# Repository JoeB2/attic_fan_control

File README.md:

# attic_fan_control
Abstract:
  In the summer, Seattle Area, it can get hot.  Last summer, 2021 we saw several days well over 100f.
  Most homes in the Seattle area are not equiped with AC.  Attic space in my home can reach 130f degrees.
  If I could programatically manage an attic fan to turn on/off depending on Attic Temps & outside temps & inside house temps 
  it may reduce inside house temps.  (TBD)
  
  Using two ESP8266 -  ESP01:
  Control a solid state "relay" SSR-25 DA to turn on/off a box fan that covers an attic access in the ceiling.
  Using two Dallas DS18B20 temp sensors, one in the Attic and one in the hallway AND a remote esp01 sensor with a DS18B20
  the Attic esp01's C++ will determine whether to turn on the solid state module for the fan. 
  
Implementation:
  The Remote esp01 will be located in the shade outside in the back yard.  Its purpose will be to send outside
  temperatures to the Attic situated esp01, providing the c++ an opportunity to "imagine what's possible."
  The remote esp01 will have a single DS18B20 and a DS3231.
  
  Attic: esp01 handles 2x DS18B20 and a 2n2222 which excites a SSR-25 DA solid state relay.
    An NTP pool is contacted once every hour to get a current time value.
    Temperatures are checked and delta and threshold values are computed periodically based on a user provided value.
    A status web page is hosted which shows the various temperature values and the Fan On/Off status
    A setting page is hosted where a user can input threshold values for managing when the Fan is On/Off.
    Attic Master uses: WiFi STA mode, ESPNOW, WebSock, Relay, 2x DS18B20, WiFi AP_Mode when unable to connect to the SPIFFS stored SSID
    
    Fan on/Off Logic:
      1) Attic sensor: Threshold to force Fan on or off
      2) Attic sensor: compare self to inside to turn on/off fan
      3) Attic sensor: compare self to remote sensor to turn on/off fan
      4) Inside sensor: compare self to remote sensor to turn on/off fan
      Order of precidence: 1, 3, 4, 2.
      Setting any threshold value to zero dissables that check.
      
      NOTE:
        WiFi connectivity: The attic esp01 uses a JSON string stored in its SPIFFS {SSID, PWD, IP, GW, Mask, isDHCP}.
        If the esp01 failes to connect or if the SPIFFS JSON credential string fails the Attic esp01 goes into "AP_MODE"
        whereby a software AP SSID: "Attic Fan WiFi Setup: 10.0.1.23" is hosted.  Pointing a browser to the AP's IP will provide a page
        where an SSID, PWD, and preferred IP:GW:Mask can be entered.  If use DHCP is checked IP,GW, Mask are not used.

    Remote: esp01 handles a single DS18B20 temp sensor and a DS3231 clock.
      The temperature reading is entered into a struct along with the current time and the struct's binary bits are broadcast using ESPNOW.
      Upon reciving the remote's espnow broadcast the Attic esp01 will broadcast, using espnow, the same struct's bit with an updated ack bit and an updated time vale.

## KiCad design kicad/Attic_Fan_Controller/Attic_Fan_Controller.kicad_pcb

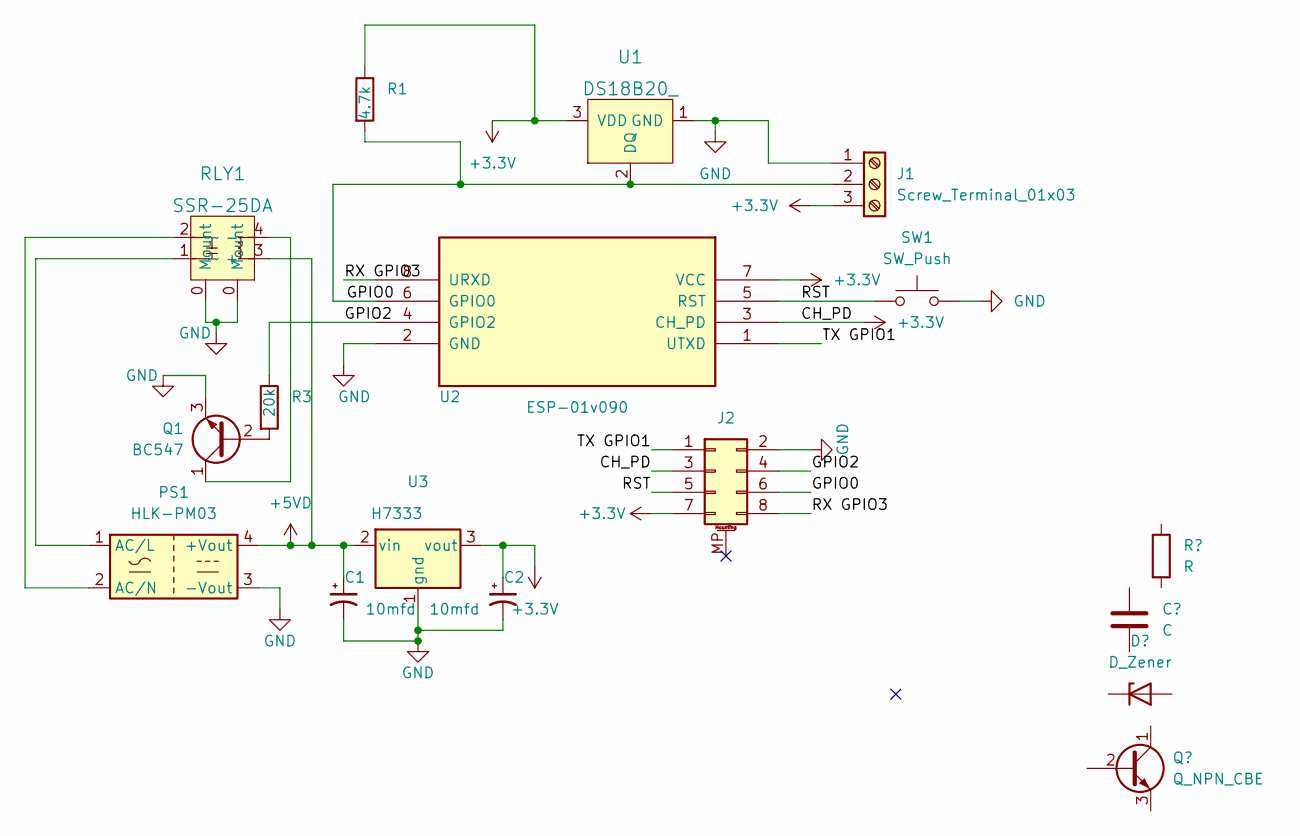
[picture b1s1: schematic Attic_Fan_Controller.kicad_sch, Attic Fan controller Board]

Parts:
C1, C2: 10mfd; CP_Radial_D4.0mm_P1.50mm
J1: Screw_Terminal_01x03; TerminalBlock_Phoenix_PT-1,5-3-5.0-H_1x03_P5.00mm_Horizontal
J2: Conn_02x04_Odd_Even_MountingPin; PinSocket_2x04_P2.54mm_Vertical
PS1: HLK-PM03; Converter_ACDC_HiLink_HLK-PMxx
Q1: BC547; TO-92_Inline
R1: 4.7k; R_Axial_DIN0207_L6.3mm_D2.5mm_P10.16mm_Horizontal
R3: 20k; R_Axial_DIN0207_L6.3mm_D2.5mm_P10.16mm_Horizontal
RLY1: SSR-25DA; SSR-25 DA; MPN 9007-05-00; Digi-Key_PN 306-1062-ND
SW1: SW_Push; SW_PUSH_6mm_H5mm
U1: DS18B20_; TO-92-3; MPN DS18B20+; Digi-Key_PN DS18B20+-ND
U2: ESP-01v090; ESP-01
U3: H7333; SOT-89-3

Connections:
+3V3: C2.1, J1.3, J2.3, J2.7, R1.1, U1.3 (VDD), U2.3 (CH_PD), U2.7 (VCC), U3.3 (vout); also elsewhere on the board
+5VD: C1.1, PS1.4 (+Vout), RLY1.3 (+), U3.2 (vin)
/GPIO0: J1.2, J2.6, R1.2, U1.2 (DQ), U2.6 (GPIO0)
/GPIO2: J2.4, R3.1, U2.4 (GPIO2); also elsewhere on the board
/RST: J2.5, SW1.1, U2.5 (RST)
/RX GPIO3: J2.8, U2.8 (URXD)
/TX GPIO1: J2.1, U2.1 (UTXD)
GND: C1.2, C2.2, J1.1, J2.2, PS1.3 (-Vout), Q1.3 (E), RLY1.0 (Mount), SW1.2, U1.1 (GND), U2.2 (GND), U3.1 (gnd)
unnamed: PS1.1 (AC/L), RLY1.1 (~~)
unnamed: PS1.2 (AC/N), RLY1.2 (~~)
unnamed: Q1.1 (C), RLY1.4 (-)
unnamed: Q1.2 (B), R3.2

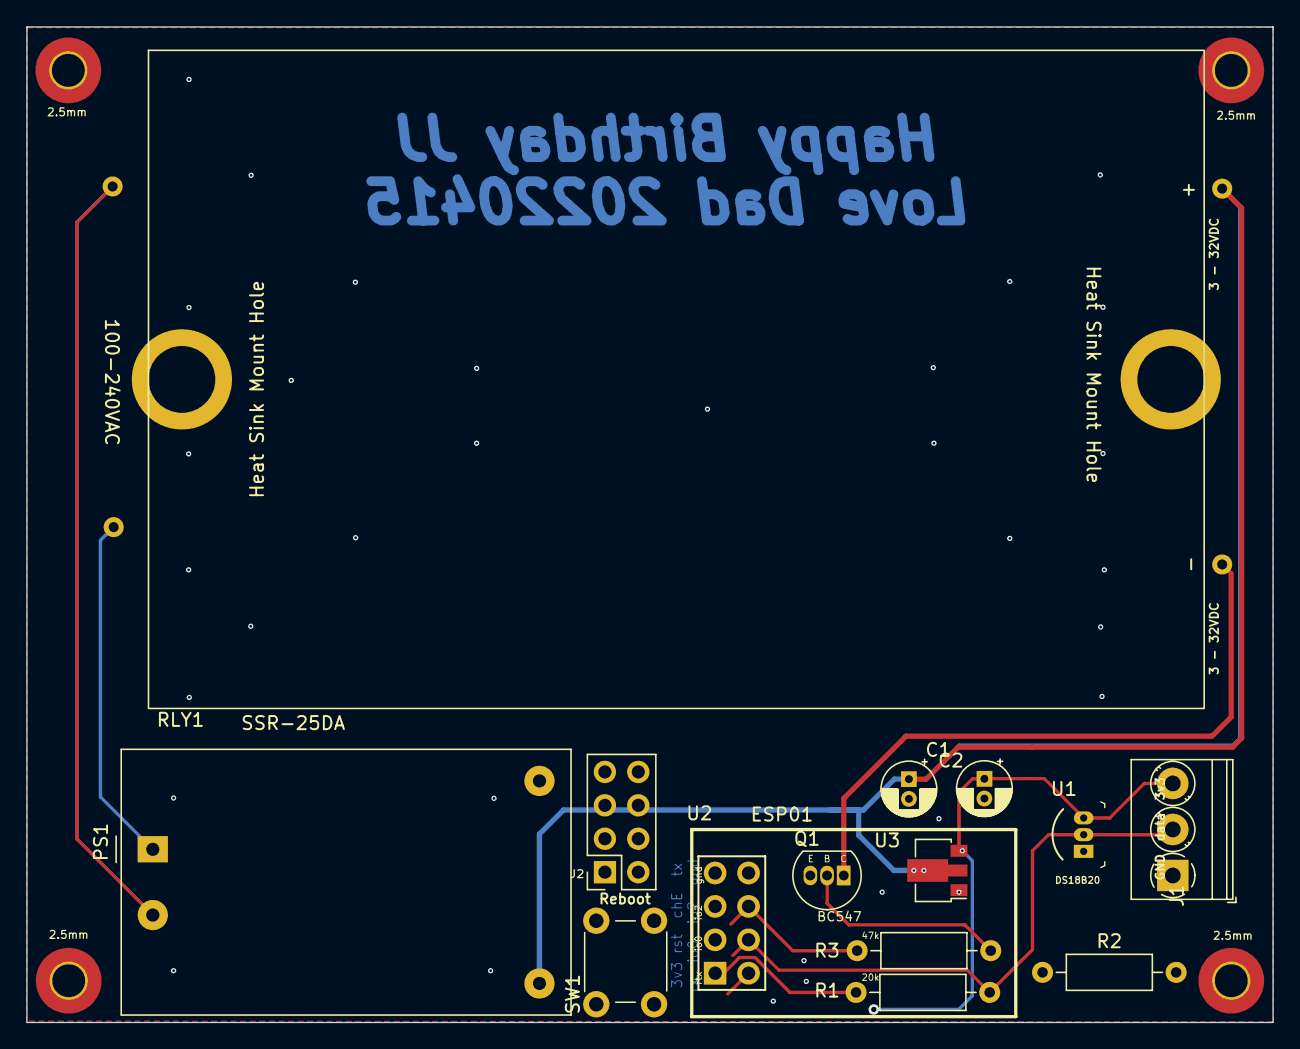
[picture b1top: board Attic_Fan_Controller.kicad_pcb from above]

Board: 2 copper layers, 94.7 x 75.7 mm, 18 parts (0 on the bottom side), 12 nets.

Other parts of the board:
2.5mm, 2.5mm#2, 2.5mm#3, 2.5mm#4: MountingHole_2.5mm_Pad_TopBottom
R2: 10k; R_Axial_DIN0207_L6.3mm_D2.5mm_P10.16mm_Horizontal

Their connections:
+3V3: R2.1; also elsewhere on the board
/GPIO2: R2.2; also elsewhere on the board

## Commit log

2022-05-26 Project Completed
2022-05-31 fixed inside_off parameter from json error
2023-07-09 Update network setting artifacts
2023-07-09 added the compilled esp01 bin file
